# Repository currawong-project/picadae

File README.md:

# Currawong Picadae

The Currawong Picadae is a portable piano player unit inspired by
[PlayerPiano II](https://logosfoundation.org/instrum_gwr/playerpiano.html) as created by [Gotfried-Willem Raes](https://en.wikipedia.org/wiki/Godfried-Willem_Raes)
 of the [Logos Foundation](https://www.logosfoundation.org/).  This project
 was a [Currawong Project](https://currawongproject.org) collaboration with
 Bill Bowen and Chico McMurtrie of [Amorphic Robot Works](https://amorphicrobotworks.org/).

# CML Picadae hardware and a control files.

- [__kicad__](kicad/README.md) contains the keyboard and pedal schematics and printed circuit board layout.
- [__control__](control/README.md) contains the keyboard solenoid ATtiny85 firware, controller Arduino firmware and, Python control API and program.

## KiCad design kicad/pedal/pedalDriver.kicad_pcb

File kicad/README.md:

# Bill of materials

## Keyboard Power and Control 

These parts serve the entire keyboard solenoid assembly.

Id   | Type            | Description          | Qty | Source   | Part Number
-----|-----------------|----------------------|-----|----------|--------------------
J3   | 6P Terminal     | Screw Terminal       |   2 | Mouser   | 651-1725698
P1   | HDS800PS24      | 24V Power Supply     |   1 | Digikey  | 1470-2689-ND
P2   | HDS800PS12      | 12V Power Supply     |   1 | Digikey  | 1470-2687-ND
P3   | TXL 015-05S     | 5V Power Supply      |   1 | Digikey  | 1951-1325-ND
M0   | Controller MCU  | Arduino Uno R3       |   1 | Digikey  | 1050-1024-ND
None | 1/16 x 1/8 x 1/2| Rubber feet(pkg 100) |   1 | McMaster | 9753K11

## Key Driver Board (11 channels per board) 

There are 8 driver boards per keyboard solenoid assembly. Each board
has 11 driver circuits.  

Id   | Type            | Description         | Qty | Source   | Part Number
-----|-----------------|---------------------|-----|----------|--------------------
U1   | ATtiny85-20MU   | Microcontroller     |  11 | Mouser   | 556-ATTINY85-20PU
None | 8DIP IC         | Socket              |  11 | Mouser   | 571-1-2199298-2
None | 0.1uF           | Capacitor           |   1 | Digikey  | 399-14010-1-ND
R1-2 | 4.7k            | Resistor            |  22 | Mouser   | 293-4.7K-RC
D1   | BYV32-200       | Diode               |  11 | Mouser   | BYV32-200GOS-ND
D2   | SF52            | Rectifier           |  11 | Mouser   | 583-SF52-B
D4   | Z10Y            | Diode               |  11 | Mouser   | 78-BZX55C10-TAP
Q1   | 2N3906          | BJT                 |  11 | Mouser   | 512-2N3906BU
Q2   | IRL640          | MOSFET              |  11 | Mouser   | 512-IRL640A
Q3   | IRF610          | MOSFET              |  11 | Mouser   | 844-IRF610PBF
S1   | Solenoid        | Ledex 195207-228    |  11 | Testco   | 195207-228
C1   | 100uF           | Capacitor           |   2 | Digikey  | 493-1668-ND
J1   | 2P Terminal     | Screw Terminal      |  11 | Mouser   | 651-1725656
J2   | 6P Female .1    | Pin Terminal        |   1 | Digikey  | H123900-ND

## Damper Pedal Driver Board

Id   | Type            | Description         | Qty | Source   | Part Number
-----|-----------------|---------------------|-----|----------|--------------------
R1-4 | 180 ohm         | Resistor            |   4 |  Mouser  | 660-MF1/2LCT52R181G
R5-6 | 470 ohm         | Resistor            |   2 |  Mouser  | 71-CCF07470RGKE36
C1-2 | 1uF             | Capacitor           |   2 |  Newark  | 65R3171
C3-4 | 4700uF          | Capacitor           |   2 |  Newark  | GBPC2501W
Q1-2 | BS170           | MOSFET              |   2 |  Mouser  | 512-BS170
Q3-4 | IRF1310NPBF     | MOSFET              |   2 |  Mouser  | 942-IRF1310NPBF
U1   | TLP523          | Dual Opto-isolator  |   1 |  Newark  | 05M1443
U2-3 | LM7810ACT       | 10V Voltage Regulato|   2 |  Mouser  | 512-KA7810ETU
D1   | Bridge Rectifier| 100V 25A            |   1 |  Newark  | GBPC2501W
D2-3 | STTH30R061PI    | Diode               |   1 |  Mouser  | 512-RURP3060
L1   | Push Solenoid   | 24 Volt             |   1 |  Laukhuff| 301010
T1   | Transformer     |                     |   1 |  Digikey | 595-1961-ND

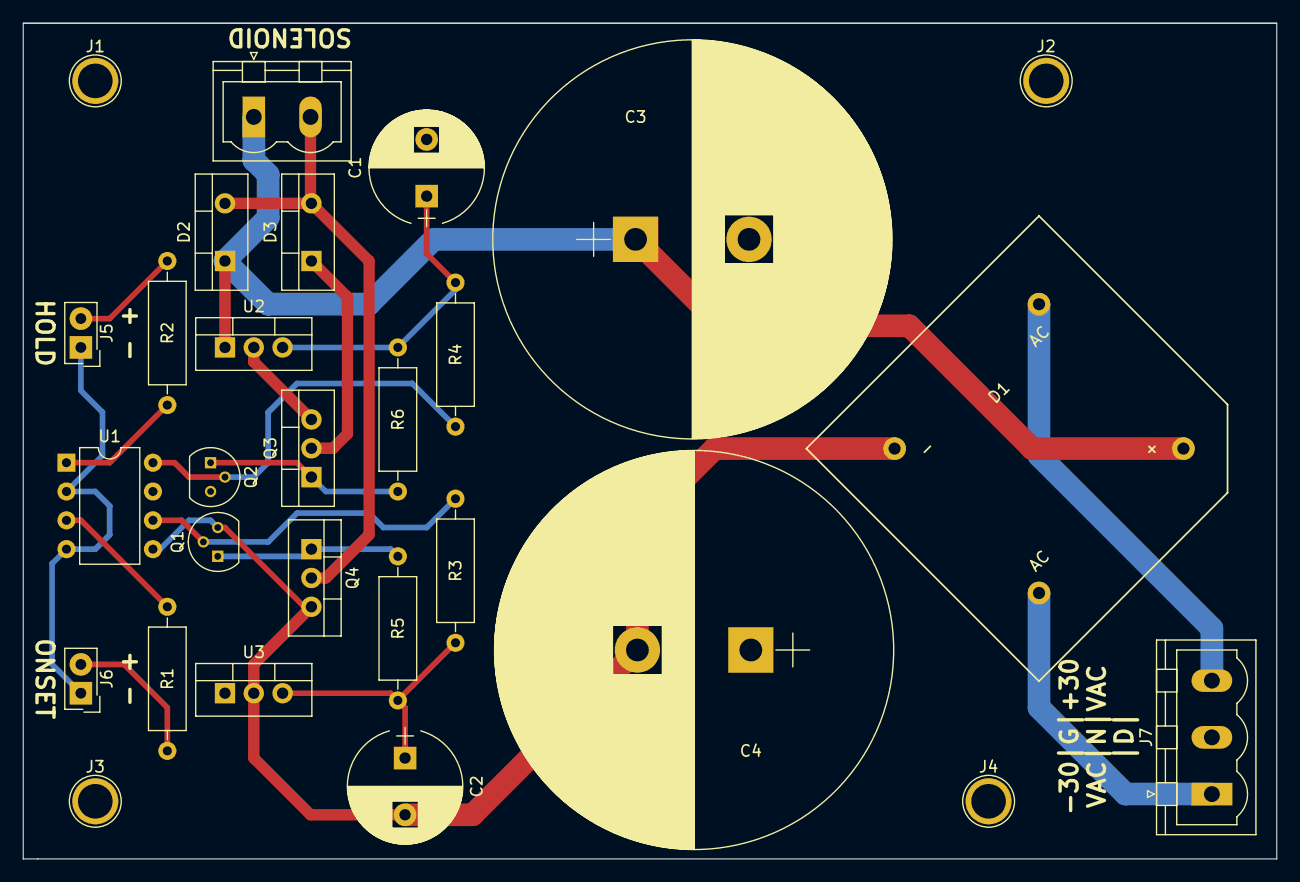
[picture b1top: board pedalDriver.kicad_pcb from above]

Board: 2 copper layers, 110.5 x 73.7 mm, 28 parts (0 on the bottom side), 18 nets.

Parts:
C1, C2: 1µF; CP_Radial_D10.0mm_P5.00mm
C3, C4: 4700µF; CP_Radial_D35.0mm_P10.00mm_SnapIn
D1: D_Bridge_+-AA; GBPC-W
D2, D3: STTH30R061PI; TO-220-2_Vertical
J1, J2, J3, J4: CONN_01X01; 1pin
J5: HOLD; SL-102-X-XX_1x02
J6: ONSET; SL-102-X-XX_1x02
J7: -30, G, 30; PhoenixContact_MSTBVA-G_03x5.00mm_Vertical
Q1, Q2: BS170; TO-92_Molded_Narrow
Q3, Q4: IRF1310NPBF; TO-220-3_Vertical
R1, R2, R3, R4: 180Ω; R_Axial_DIN0309_L9.0mm_D3.2mm_P12.70mm_Horizontal
R5, R6: 470Ω; R_Axial_DIN0309_L9.0mm_D3.2mm_P12.70mm_Horizontal
Solenoid1: 20Ω; PhoenixContact_MSTBVA-G_02x5.00mm_Vertical
U1: TLP523-2; DIP-8_W7.62mm
U2, U3: LM7810ACT; TO-220-3_Vertical

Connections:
30VAC+: D1.3, J7.3
30VAC-: D1.4, J7.1
GND: C1.2, C3.2, C4.1, J7.2, Q2.3, Q3.3, U1.7, U2.2, U3.1
Hold: J5.2, R2.2
unnamed: C1.1, R4.2, R6.2, U2.3
unnamed: C2.1, R3.2, R5.2, U3.3
unnamed: C2.2, C4.2, D1.2, Q1.3, Q4.3, U1.5, U3.2
unnamed: C3.1, D1.1, D2.1, Solenoid1.1, U2.1
unnamed: D2.2, D3.2, Q4.2, Solenoid1.2
unnamed: D3.1, Q3.2
unnamed: Q1.1, Q4.1, R5.1
unnamed: Q1.2, R3.1, U1.6
unnamed: Q2.1, Q3.1, R6.1
unnamed: Q2.2, R4.1, U1.8
unnamed: R1.1, U1.3
unnamed: R2.1, U1.1
Onset: J6.2, R1.2
dGND: J5.1, J6.1, U1.2, U1.4

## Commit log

2019-07-07 Added picadae/
2019-07-14 i2c_timer_pwm.c initial PWM initialization.
2019-07-14 Initial working version of long interval timer and PWM under the control of picadae_cmd.py.
2019-07-20 picadae_cmd.py : changed serial output to show all received data in integer format. ctrl/main.c : write commands now send as many data bytes as received rather than just 2. tiny/main.c : Added timer0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
2019-08-03 Updates for initial timer and pwm test on piccadae.
2019-08-07 Updates to support 16Mhz and reading from register memory from picadae_shell.py.
2019-08-08 picadae_api.py : Implemented Table write and read. Added set/get_mode().
2019-08-08 ctrl/main.c, tiny/i2c_timer_pwm.c : Updated comments.
2019-08-20 Added table writing (not yet tested) and removed 'repeat-mode'.
2019-09-01 Added make_seq() to picadae_api.py and picadae_shell.py
2019-09-01 Added earlier and extended versions of picadae/tiny/i2c_timer_pwn*.c in the folder picadae/tiny/versions
2019-09-14 Clear TCNTx registers at start of attack and hold. Reverse polarity of hold output.
2019-11-18 picadae/ctrl/Makefile,main.c : Added code to allow ATMega2560 as target.
2019-11-18 picadae/tiny/i2c_timer_pwm.c : Added 'hold_state' to cleanly set the enable/disable PCM.
2019-11-18 picadae/app/picadae_api.py, picadae_shell.py : Updated PWM settters and getters.
2020-10-21 kicad/ : Initial commit
2020-10-21 kicad/README.md : initial commit
2020-10-21 README.md : initial commit.
2020-10-21 kicad/README.md : More updates.
2020-10-21 kicad/README.md,keyboard.png,pedal.png : Add images to the kicad readme.
2020-10-21 kicad/keyboard.png : Updated
2020-10-24 control/README.md : Initial commit.
2020-10-24 README.md : Updated.
2020-10-26 LICENSE and COPYRIGHT : Initial commit. Added license notice to all code files and schematics.
2020-11-22 tiny/i2c_timer_pwm.c : Added hold delay and other changes to validate operation after logic analyzer analysis.
2020-11-22 app/picadae_api.py, picadae_shell.py : Added set/get_hold_delay(). Fixed shell._read().
2020-11-24 app/README.md,tiny/README.md,ctrl/READM.md : Initial commit.
2020-11-24 README.md : Update
2020-11-24 tiny/README.md : Updates
2020-11-24 app/README.md : Updates
2020-12-07 README.md : Added image
2020-12-07 picadae_api.py,picadae_shell.py : Added 'flags' parameter and 'make_scale' API.
2020-12-07 tiny/usiTwiSlave.h/c : Make usi_onRequestPtr,usi_onRecievePtr extern and include <stdddef.h> to fix compilation errors apparently caused by new version of compiler.
2020-12-07 tiny/i2c_timer_pwm_2.c,tinyMakefile : New firmware version with programmable hold delay.
2020-12-07 picadae_solenoids_closeup_20191012_2.jpg : initial commit
2020-12-07 .gitignore : Initial commit.
2020-12-07 README.me : Updates
2024-08-30 Added parts list.
2025-05-29 Updated README.
